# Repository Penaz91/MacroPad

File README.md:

My Macropad Project
====================

!! This circuit has been tested and it has been working great for a few months, but I take no responsibility for any damage or loss that comes from this project !!

This is the project of a MicroPython-programmable (via [KMK](http://kmkfw.io/)) Macro Pad using a Raspberry Pi Zero and some components.

This came from the fact that no available Commercial Mechanical Macro Pad has 20 Keys and 4 Rotary Encoders, plus their configuration programs don't really look flexible enough for my taste.

Required Software
-----------------

You will need to following software to open and edit this project:

- [KiCad](https://www.kicad.org/) 7.0.9 or Higher: for the Schematic Files
- Any CAD Program (Like [FreeCad](https://www.freecad.org/)) that supports DXF Files: for viewing the plate

Known Issues
------------

- ERC Shows "Input Power pin not driven by any Output Power pins" on U1 for pins:
    - Pin 13 (GND)
    - Pin 36 (3V3)
- DRC Shows 16 Violations "Silkscreen clipped by solder mask"

I have no idea how to fix these.

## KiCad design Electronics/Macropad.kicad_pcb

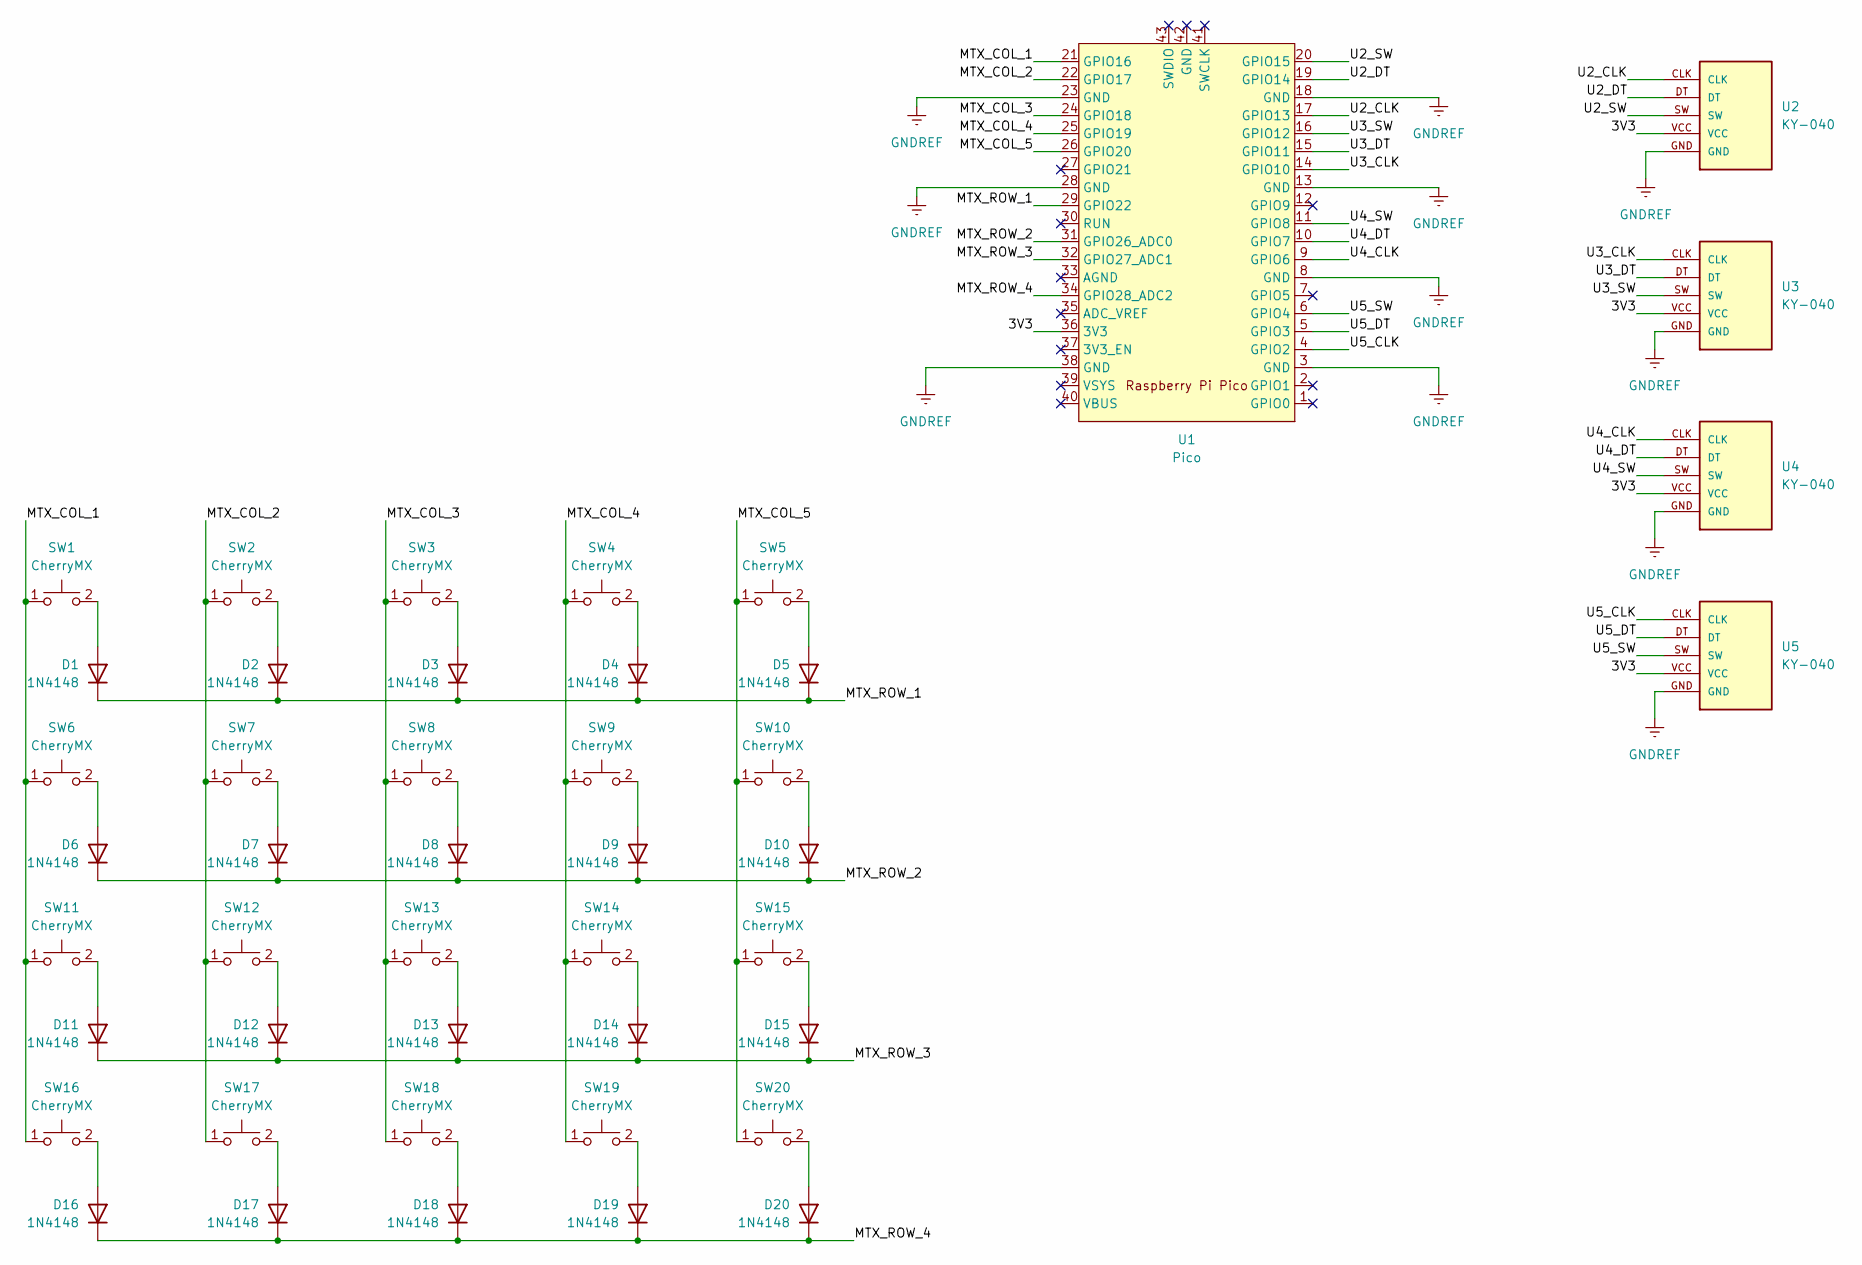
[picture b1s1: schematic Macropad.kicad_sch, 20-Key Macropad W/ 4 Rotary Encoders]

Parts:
D1, D2, D3, D4, D5, D6, D7, D8, D9, D10, D11, D12, D13, D14, D15, D16, D17, D18, D19, D20: 1N4148; D_DO-35_P7.62mm_Horizontal
SW1, SW2, SW3, SW4, SW5, SW6, SW7, SW8, SW9, SW10, SW11, SW12, SW13, SW14, SW15, SW16, SW17, SW18, SW19, SW20: CherryMX; SW_Cherry_MX_PCB
U1: Pico; RPi_Pico_SMD_TH
U2, U3, U4, U5: KY-040; KY-040-PORT

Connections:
/3V3: U1.36 (3V3), U2.VCC, U3.VCC, U4.VCC, U5.VCC
/MTX_COL_1: SW1.1, SW6.1, SW11.1, SW16.1, U1.21 (GPIO16)
/MTX_COL_2: SW2.1, SW7.1, SW12.1, SW17.1, U1.22 (GPIO17)
/MTX_COL_3: SW3.1, SW8.1, SW13.1, SW18.1, U1.24 (GPIO18)
/MTX_COL_4: SW4.1, SW9.1, SW14.1, SW19.1, U1.25 (GPIO19)
/MTX_COL_5: SW5.1, SW10.1, SW15.1, SW20.1, U1.26 (GPIO20)
/MTX_ROW_1: D1.1 (K), D2.1 (K), D3.1 (K), D4.1 (K), D5.1 (K), U1.29 (GPIO22)
/MTX_ROW_2: D6.1 (K), D7.1 (K), D8.1 (K), D9.1 (K), D10.1 (K), U1.31 (GPIO26_ADC0)
/MTX_ROW_3: D11.1 (K), D12.1 (K), D13.1 (K), D14.1 (K), D15.1 (K), U1.32 (GPIO27_ADC1)
/MTX_ROW_4: D16.1 (K), D17.1 (K), D18.1 (K), D19.1 (K), D20.1 (K), U1.34 (GPIO28_ADC2)
/U2_CLK: U1.17 (GPIO13), U2.CLK
/U2_DT: U1.19 (GPIO14), U2.DT
/U2_SW: U1.20 (GPIO15), U2.SW
/U3_CLK: U1.14 (GPIO10), U3.CLK
/U3_DT: U1.15 (GPIO11), U3.DT
/U3_SW: U1.16 (GPIO12), U3.SW
/U4_CLK: U1.9 (GPIO6), U4.CLK
/U4_DT: U1.10 (GPIO7), U4.DT
/U4_SW: U1.11 (GPIO8), U4.SW
/U5_CLK: U1.4 (GPIO2), U5.CLK
/U5_DT: U1.5 (GPIO3), U5.DT
/U5_SW: U1.6 (GPIO4), U5.SW
GNDREF: U1.3 (GND), U1.8 (GND), U1.13 (GND), U1.18 (GND), U1.23 (GND), U1.28 (GND), U1.38 (GND), U2.GND, U3.GND, U4.GND, U5.GND
unnamed: D1.2 (A), SW1.2
unnamed: D2.2 (A), SW2.2
unnamed: D3.2 (A), SW3.2
unnamed: D4.2 (A), SW4.2
unnamed: D5.2 (A), SW5.2
unnamed: D6.2 (A), SW6.2
unnamed: D7.2 (A), SW7.2
unnamed: D8.2 (A), SW8.2
unnamed: D9.2 (A), SW9.2
unnamed: D10.2 (A), SW10.2
unnamed: D11.2 (A), SW11.2
unnamed: D12.2 (A), SW12.2
unnamed: D13.2 (A), SW13.2
unnamed: D14.2 (A), SW14.2
unnamed: D15.2 (A), SW15.2
unnamed: D16.2 (A), SW16.2
unnamed: D17.2 (A), SW17.2
unnamed: D18.2 (A), SW18.2
unnamed: D19.2 (A), SW19.2
unnamed: D20.2 (A), SW20.2

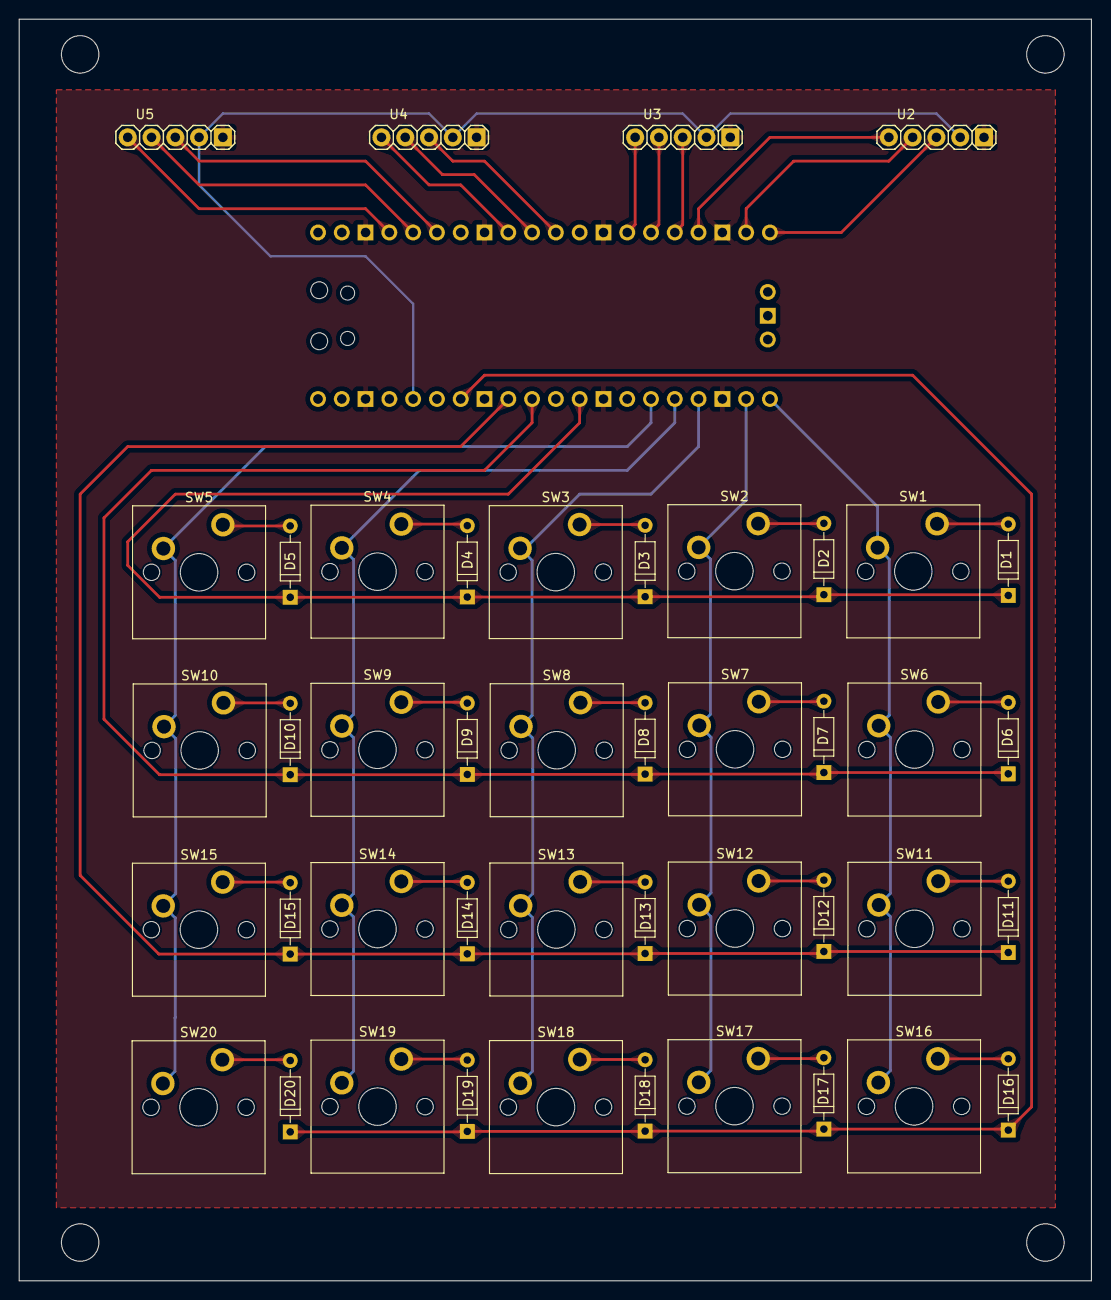
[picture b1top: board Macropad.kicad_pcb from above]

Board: 2 copper layers, 114.5 x 134.7 mm, 45 parts (1 on the bottom side), 43 nets.

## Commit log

2023-11-14 Revision 1
2023-11-15 Added known issues
2023-11-23 Added more exclusions
2023-11-23 Removed Gerbers, fixed row/column diode inversion
2024-05-10 Update Kicad
